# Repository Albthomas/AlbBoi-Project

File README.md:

# AlbBoi-Project
This is a project that encompasses PCB design, microcontroller programming in C, Schematic Design, 3D, and CAD modeling. My project is to create a device similar to a Gameboy using the ATSAML21J18B microcontroller. The final product is a PCB with a 3D printed enclosure that will allow users to play games.

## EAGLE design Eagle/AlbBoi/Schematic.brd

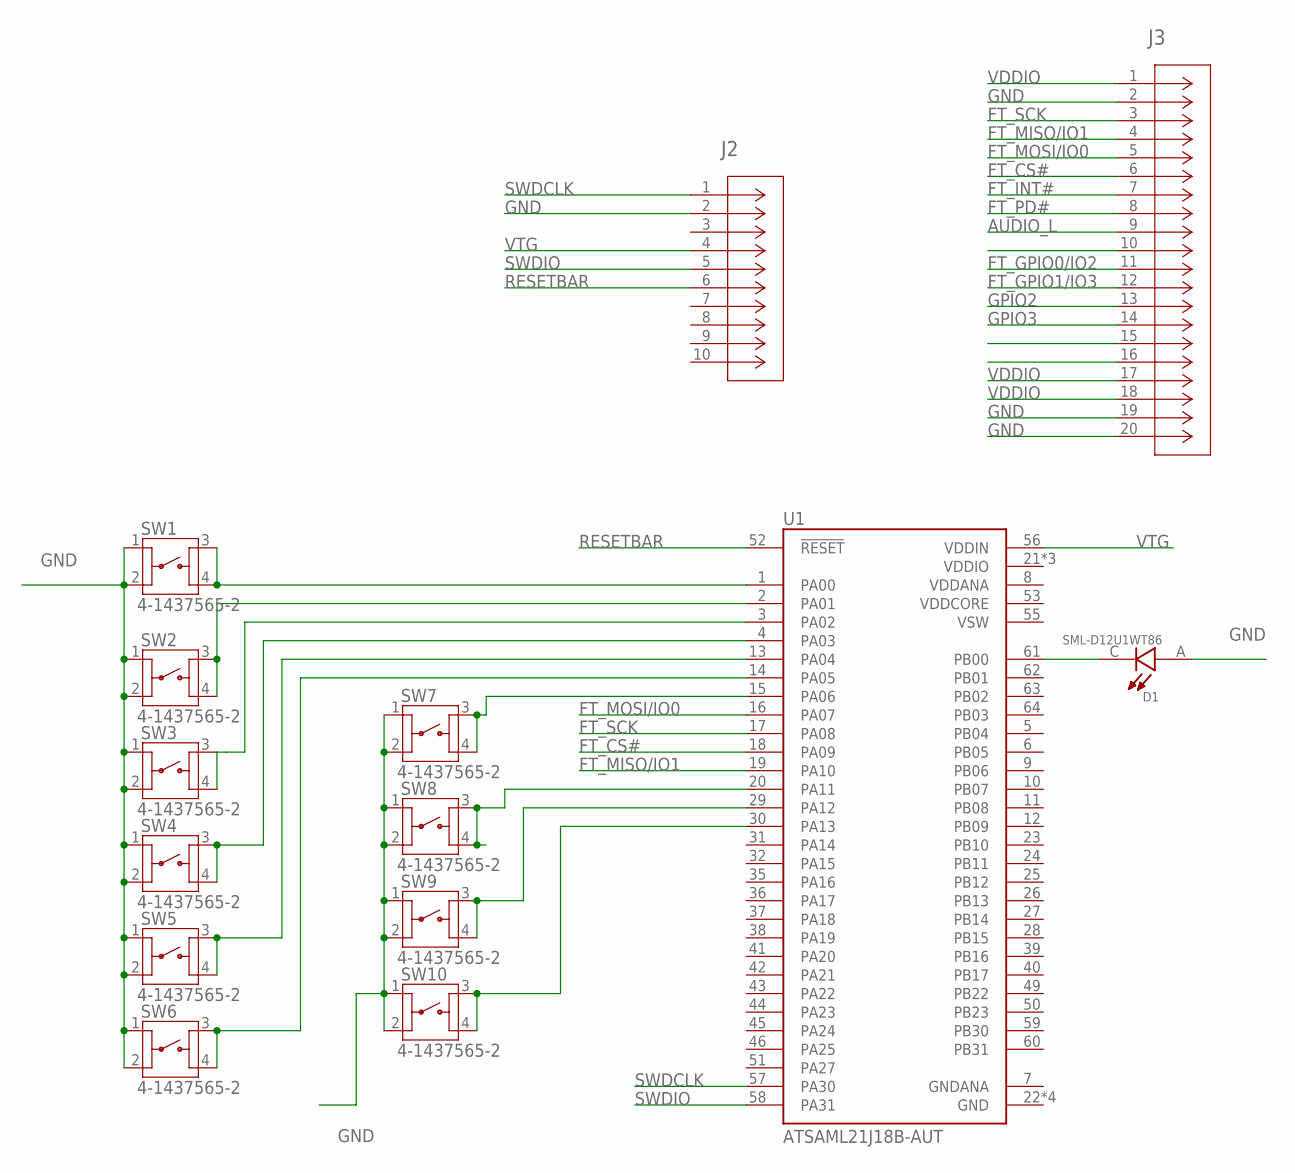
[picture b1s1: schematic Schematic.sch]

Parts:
D1: SML-D12U1WT86; LED_SML-D12Y1WT86
J2: 20021121-00010C4LF; CONN_00010C4LF_AMP
J3: SBH11-NBPC-D10-SM-BK; CONN_SBH11-NBPC-D10-SM-BK
SW1, SW2, SW3, SW4, SW5, SW6, SW7, SW8, SW9, SW10: 4-1437565-2; SW_4-1437565-2
U1: ATSAML21J18B-AUT; QFP50P1200X1200X120-64N

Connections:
AUDIO_L: J3.9
FT_CS#: J3.6, U1.18 (PA09)
FT_GPIO0/IO2: J3.11
FT_GPIO1/IO3: J3.12
FT_INT#: J3.7
FT_MISO/IO1: J3.4, U1.19 (PA10)
FT_MOSI/IO0: J3.5, U1.16 (PA07)
FT_PD#: J3.8
FT_SCK: J3.3, U1.17 (PA08)
GND: D1.A, J2.2, J3.2, J3.19, J3.20, SW1.1, SW1.2, SW2.1, SW2.2, SW3.1, SW3.2, SW4.1, SW4.2, SW5.1, SW5.2, SW6.1, SW6.2, SW7.1, SW7.2, SW8.1, SW8.2, SW9.1, SW9.2, SW10.1, SW10.2, U1.22 (GND), U1.33 (GND), U1.47 (GND), U1.54 (GND)
GNDANA: U1.7 (GNDANA)
GPIO2: J3.13
GPIO3: J3.14
unnamed: SW1.3, SW1.4, U1.1 (PA00)
unnamed: SW2.3, SW2.4, U1.2 (PA01)
unnamed: SW3.3, SW3.4, U1.3 (PA02)
unnamed: SW4.3, SW4.4, U1.4 (PA03)
unnamed: SW5.3, SW5.4, U1.13 (PA04)
unnamed: SW6.3, SW6.4, U1.14 (PA05)
unnamed: SW7.3, SW7.4, U1.15 (PA06)
unnamed: SW8.3, SW8.4, U1.20 (PA11)
unnamed: SW9.3, SW9.4, U1.29 (PA12)
unnamed: SW10.3, SW10.4, U1.30 (PA13)
unnamed: D1.C, U1.61 (PB00)
RESETBAR: J2.6, U1.52 (!RESET)
SWDCLK: J2.1, U1.57 (PA30)
SWDIO: J2.5, U1.58 (PA31)
VDDANA: U1.8 (VDDANA)
VDDCORE: U1.53 (VDDCORE)
VDDIO: J3.1, J3.17, J3.18, U1.21 (VDDIO), U1.34 (VDDIO), U1.48 (VDDIO)
VSW: U1.55 (VSW)
VTG: J2.4, U1.56 (VDDIN)

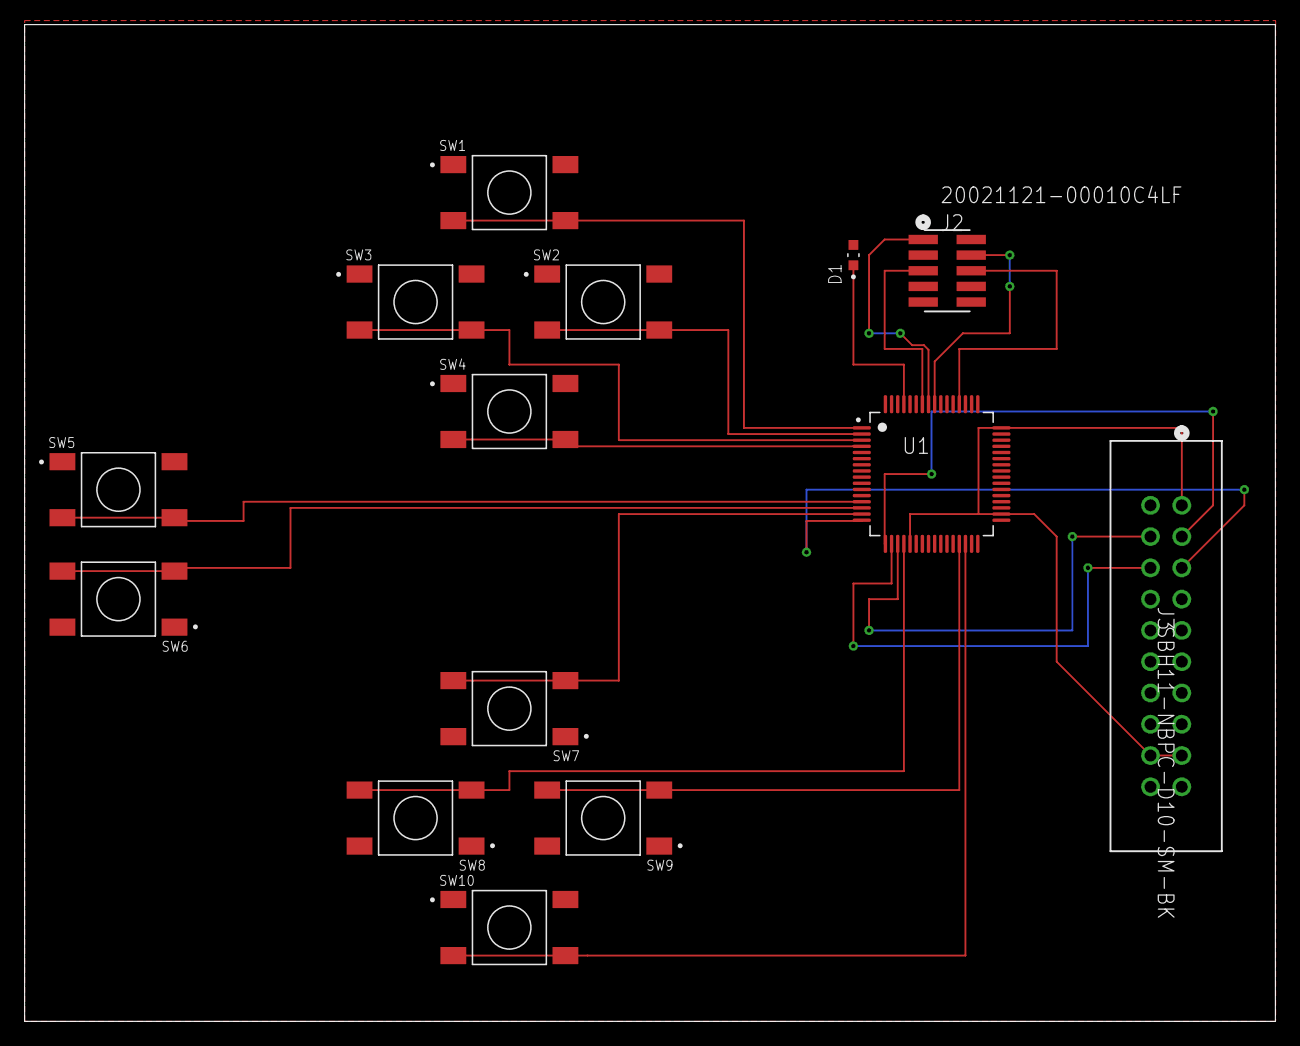
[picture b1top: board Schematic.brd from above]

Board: 2 copper layers, 101.6 x 81.0 mm, 14 parts (0 on the bottom side), 21 nets.

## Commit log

2020-05-28 Images of Designs post Spring 2020 Semester
    These are images of my designs that correspond to where my project was after the Spring 2020 semester ended.
2020-05-28 Create temp
2020-05-28 Add Schematic Image
2020-05-28 CAD Images
2020-05-28 PCB Image
2020-06-03 Adding Eagle Schematic
2020-06-03 Contains 3d model of the case
    Case and board 3d models are included
2020-06-11 Adding BOM

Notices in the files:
parts and their libraries:
COPYRIGHT: Copyright (C) 2018 Accelerated Designs. All rights reserved
